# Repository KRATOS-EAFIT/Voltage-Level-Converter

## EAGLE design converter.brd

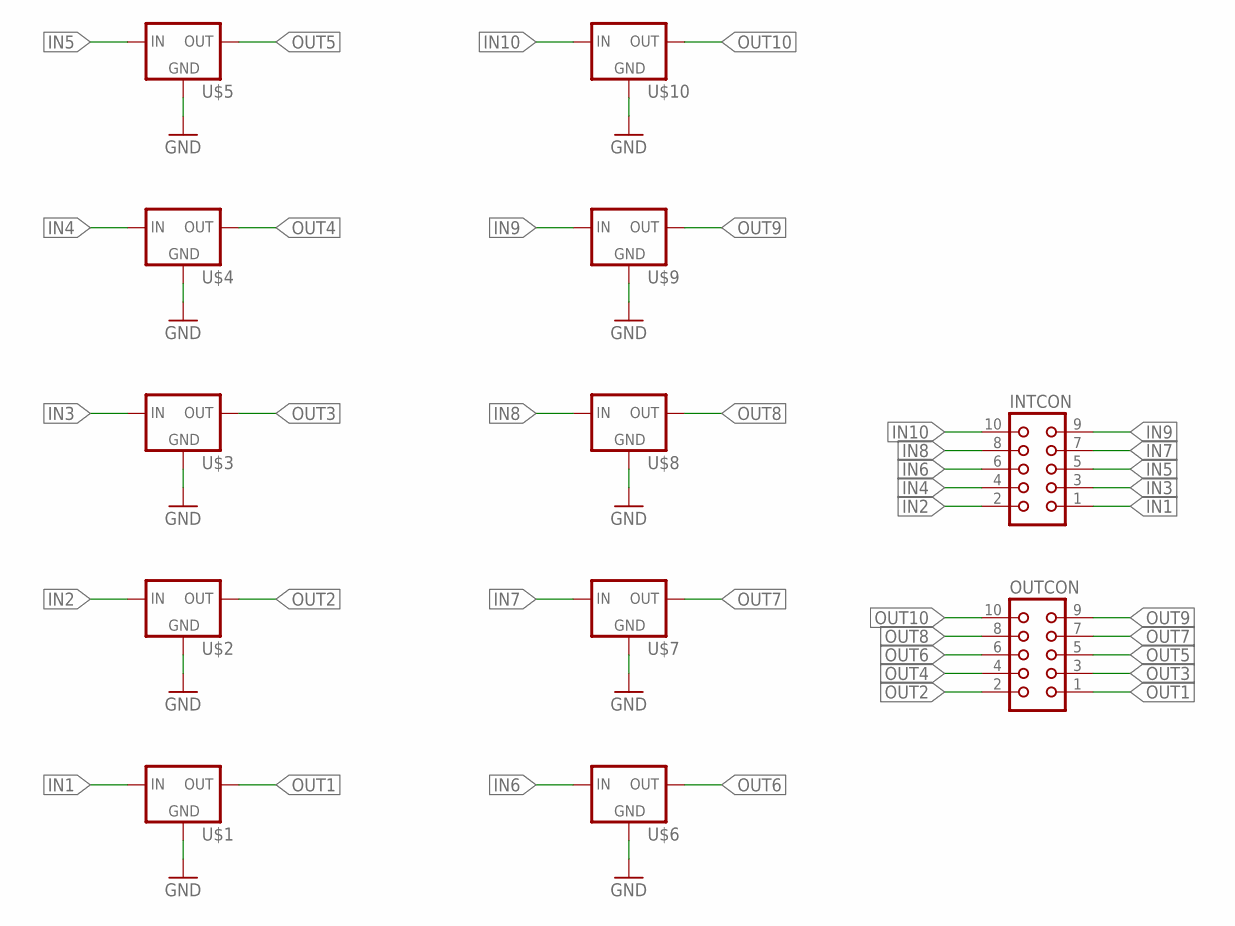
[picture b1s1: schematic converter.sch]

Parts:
INTCON: CON10
OUTCON: CON10
U$1, U$2, U$3, U$4, U$5, U$6, U$7, U$8, U$9, U$10: LOGIC_CONVERTERIC; SOT223

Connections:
GND: U$1.2 (GND), U$1.3 (GND), U$1.4 (GND), U$1.GND, U$2.2 (GND), U$2.3 (GND), U$2.4 (GND), U$2.GND, U$3.2 (GND), U$3.3 (GND), U$3.4 (GND), U$3.GND, U$4.2 (GND), U$4.3 (GND), U$4.4 (GND), U$4.GND, U$5.2 (GND), U$5.3 (GND), U$5.4 (GND), U$5.GND, U$6.2 (GND), U$6.3 (GND), U$6.4 (GND), U$6.GND, U$7.2 (GND), U$7.3 (GND), U$7.4 (GND), U$7.GND, U$8.2 (GND), U$8.3 (GND), U$8.4 (GND), U$8.GND, U$9.2 (GND), U$9.3 (GND), U$9.4 (GND), U$9.GND, U$10.2 (GND), U$10.3 (GND), U$10.4 (GND), U$10.GND
IN1: INTCON.1, U$1.1 (IN), U$1.IN
IN2: INTCON.2, U$2.1 (IN), U$2.IN
IN3: INTCON.3, U$3.1 (IN), U$3.IN
IN4: INTCON.4, U$4.1 (IN), U$4.IN
IN5: INTCON.5, U$5.1 (IN), U$5.IN
IN6: INTCON.6, U$6.1 (IN), U$6.IN
IN7: INTCON.7, U$7.1 (IN), U$7.IN
IN8: INTCON.8, U$8.1 (IN), U$8.IN
IN9: INTCON.9, U$9.1 (IN), U$9.IN
IN10: INTCON.10, U$10.1 (IN), U$10.IN
OUT1: OUTCON.1, U$1.5 (OUT), U$1.OUT
OUT2: OUTCON.2, U$2.5 (OUT), U$2.OUT
OUT3: OUTCON.3, U$3.5 (OUT), U$3.OUT
OUT4: OUTCON.4, U$4.5 (OUT), U$4.OUT
OUT5: OUTCON.5, U$5.5 (OUT), U$5.OUT
OUT6: OUTCON.6, U$6.5 (OUT), U$6.OUT
OUT7: OUTCON.7, U$7.5 (OUT), U$7.OUT
OUT8: OUTCON.8, U$8.5 (OUT), U$8.OUT
OUT9: OUTCON.9, U$9.5 (OUT), U$9.OUT
OUT10: OUTCON.10, U$10.5 (OUT), U$10.OUT

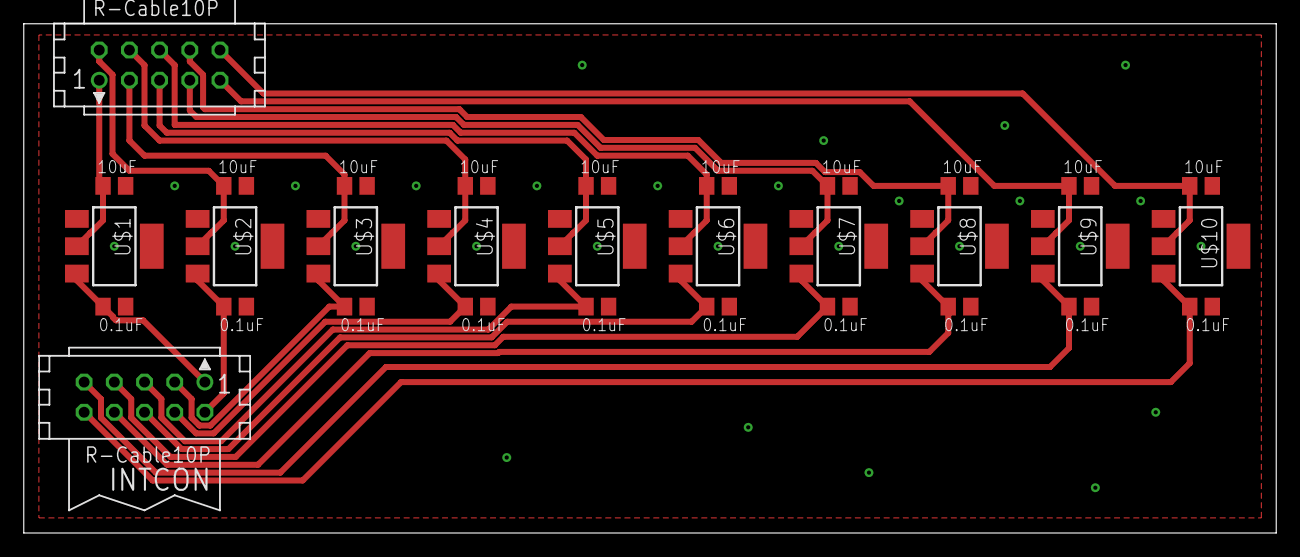
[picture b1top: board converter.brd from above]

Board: 2 copper layers, 105.4 x 42.8 mm, 12 parts (0 on the bottom side), 21 nets.

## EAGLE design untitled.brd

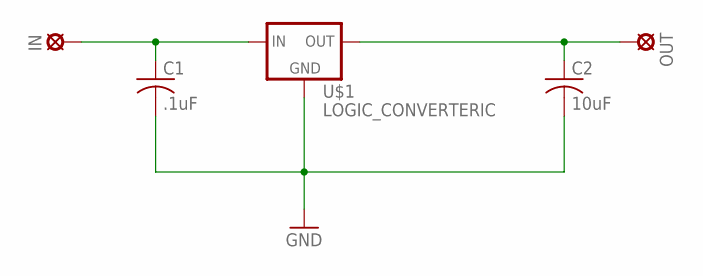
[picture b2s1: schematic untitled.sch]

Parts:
C1: .1uF; C0805K
C2: 10uF; C0805K
IN: LSP10
OUT: LSP10
U$1: LOGIC_CONVERTERIC; SOT223

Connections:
GND: C1.2, C2.2, U$1.GND
unnamed: C1.1, IN.MP, U$1.IN
unnamed: C2.1, OUT.MP, U$1.OUT

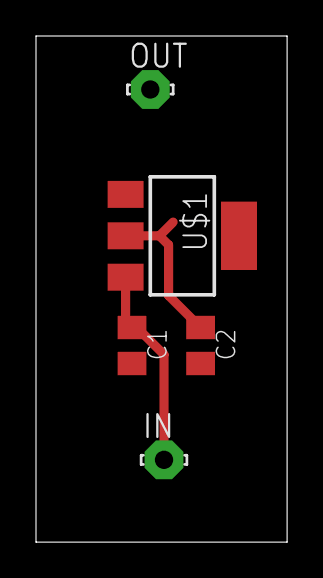
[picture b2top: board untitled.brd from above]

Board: 2 copper layers, 13.9 x 28.1 mm, 5 parts (0 on the bottom side), 3 nets.

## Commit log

2018-05-02 Tarjeta terminada
